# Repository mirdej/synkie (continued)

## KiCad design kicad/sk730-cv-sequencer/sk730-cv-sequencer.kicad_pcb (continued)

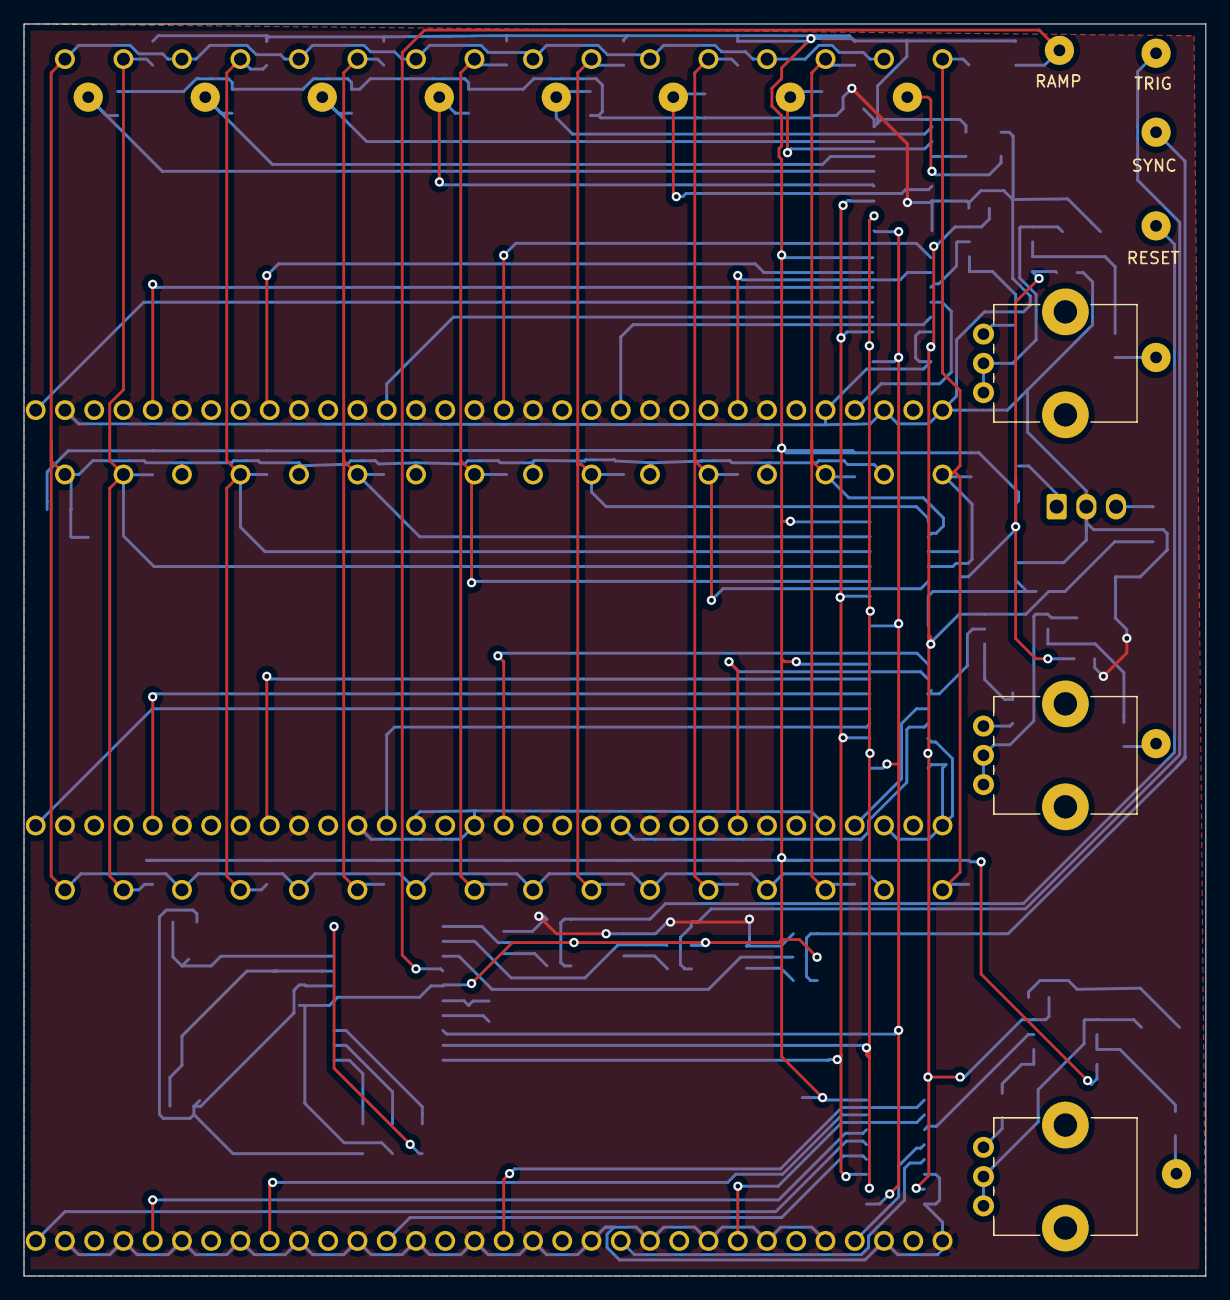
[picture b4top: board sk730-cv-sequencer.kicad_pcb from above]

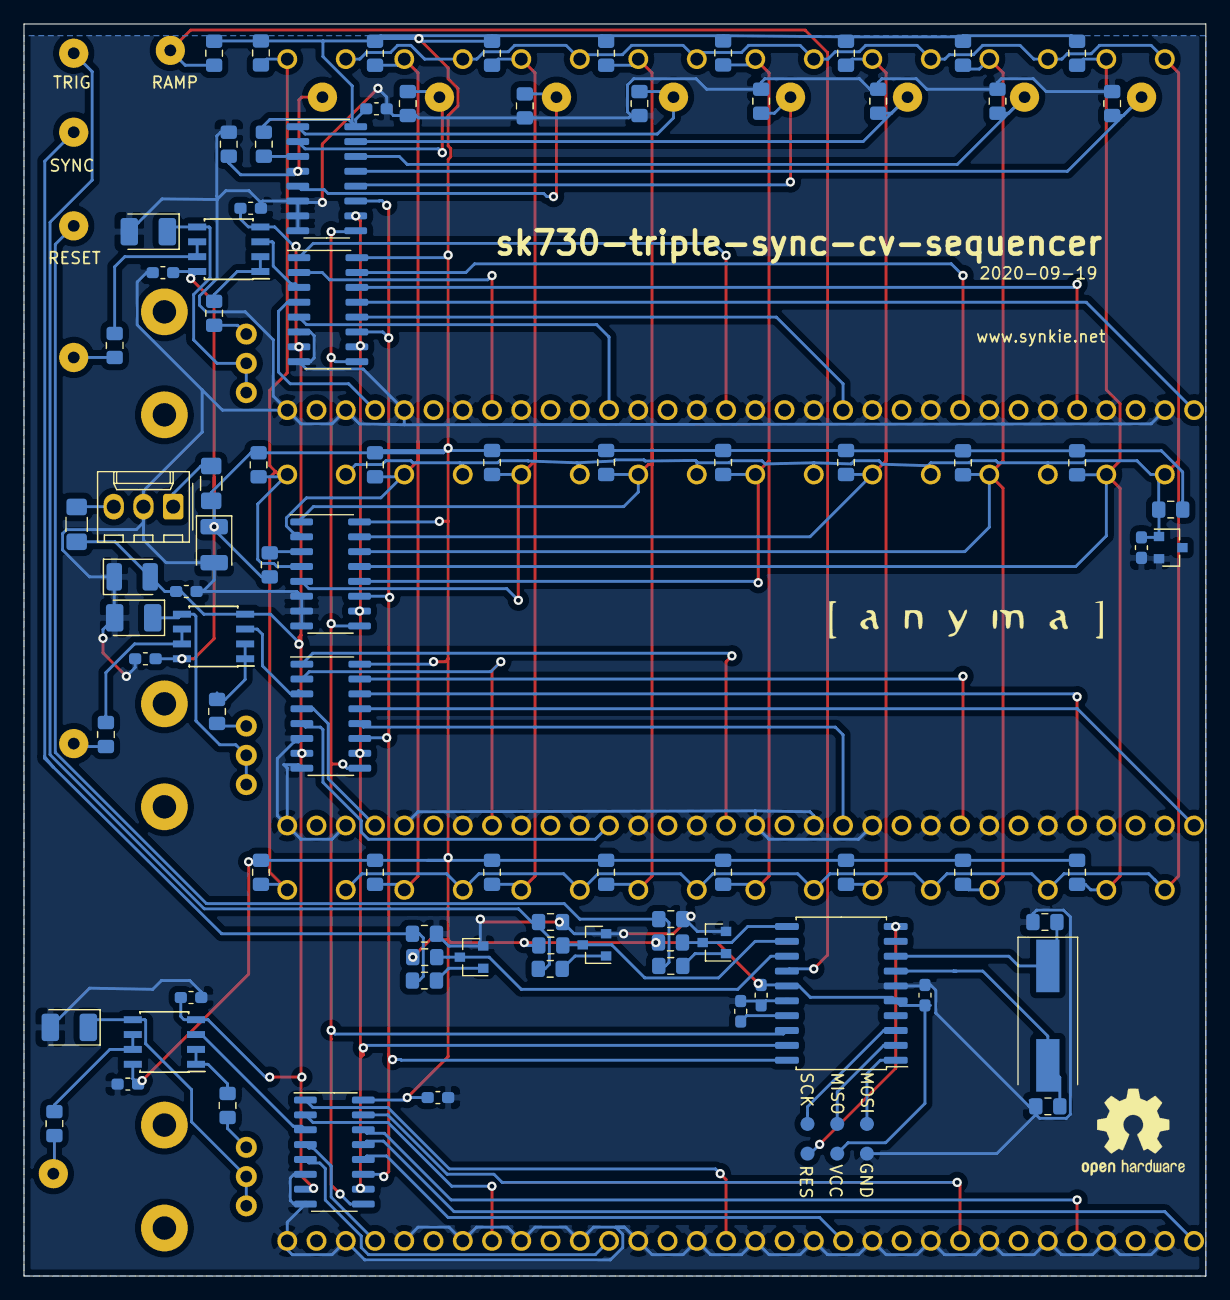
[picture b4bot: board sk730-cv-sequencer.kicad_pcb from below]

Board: 2 copper layers, 101.0 x 107.0 mm, 130 parts (103 on the bottom side), 86 nets.

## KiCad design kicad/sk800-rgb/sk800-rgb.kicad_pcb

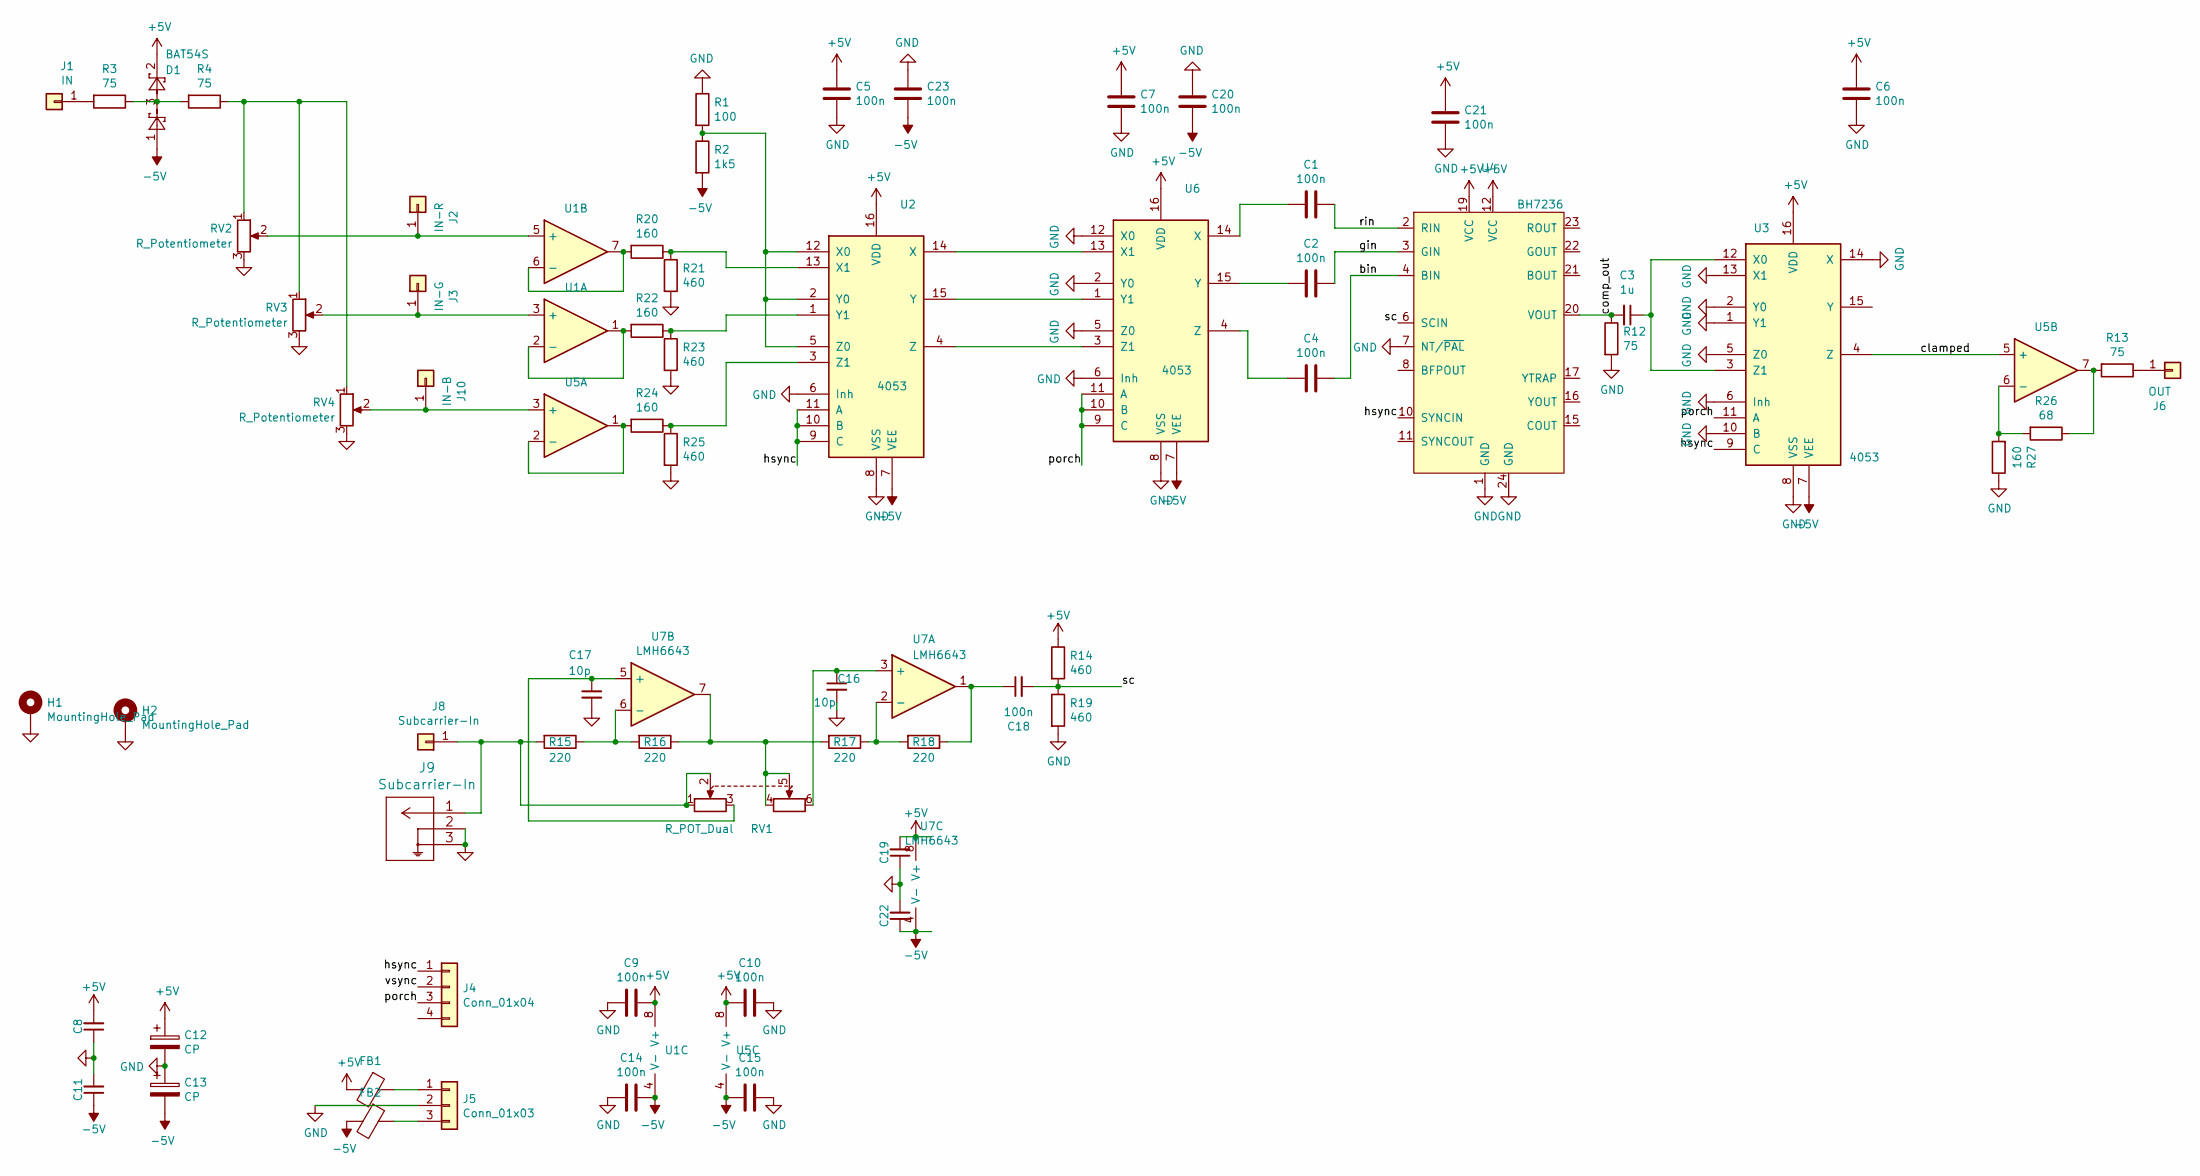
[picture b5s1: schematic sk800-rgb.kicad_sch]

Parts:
C1, C2, C4, C5, C6, C7, C8, C9, C10, C11, C14, C15, C18, C19, C20, C21, C22, C23: 100n; C_0603_1608Metric_Pad1.05x0.95mm_HandSolder
C3: 1u; C_0603_1608Metric_Pad1.05x0.95mm_HandSolder
C12, C13: CP; C_1206_3216Metric_Pad1.42x1.75mm_HandSolder
C16, C17: 10p; C_0805_2012Metric_Pad1.15x1.40mm_HandSolder
D1: BAT54S; SOT-23
FB1, FB2: Ferrite_Bead; L_0805_2012Metric_Pad1.15x1.40mm_HandSolder
H1, H2: MountingHole_Pad; MountingHole_3.2mm_M3_DIN965_Pad
J1: IN; Solderpad-SYNKIEPAD-2mm
J2: IN-R; Solderpad-SYNKIEPAD-2mm
J3: IN-G; Solderpad-SYNKIEPAD-2mm
J4: Conn_01x04; Molex_KK-254_AE-6410-04A_1x04_P2.54mm_Vertical
J5: Conn_01x03; Molex_KK-254_AE-6410-03A_1x03_P2.54mm_Vertical
J6: OUT; Solderpad-SYNKIEPAD-2mm
J8: Subcarrier-In; Solderpad-SYNKIEPAD-2mm
J9: Subcarrier-In; TE_UMCC_2337019-1
J10: IN-B; Solderpad-SYNKIEPAD-2mm
R1: 100; R_0805_2012Metric_Pad1.15x1.40mm_HandSolder
R2: 1k5; R_0805_2012Metric_Pad1.15x1.40mm_HandSolder
R3, R4, R12, R13: 75; R_0805_2012Metric_Pad1.15x1.40mm_HandSolder
R14, R19, R21, R23, R25: 460; R_0805_2012Metric_Pad1.15x1.40mm_HandSolder
R15, R16, R17, R18: 220; R_0805_2012Metric_Pad1.15x1.40mm_HandSolder
R20, R22, R24, R27: 160; R_0805_2012Metric_Pad1.15x1.40mm_HandSolder
R26: 68; R_0805_2012Metric_Pad1.15x1.40mm_HandSolder
RV1: R_POT_Dual; RK12L123
RV2, RV3, RV4: R_Potentiometer; Potentiometer_Uwe_100k
U1, U5: Opamp_Dual_Generic; SOIC-8_3.9x4.9mm_P1.27mm
U2, U3, U6: 4053; SOIC-16_3.9x9.9mm_P1.27mm
U4: BH7236; SOP-24_7.5x15.4mm_P1.27mm
U7: LMH6643; SOIC-8_3.9x4.9mm_P1.27mm

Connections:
+5V: C5.1, C6.1, C7.1, C8.2, C9.1, C10.2, C12.1, C19.2, C21.1, D1.2, FB1.2, R14.1, U1.8 (V+), U2.16 (VDD), U3.16 (VDD), U4.12 (VCC), U4.19 (VCC), U5.8 (V+), U6.16 (VDD), U7.8 (V+)
-5V: C11.1, C13.2, C14.1, C15.2, C20.2, C22.1, C23.2, D1.1, FB2.2, R2.2, U1.4 (V-), U2.7 (VEE), U3.7 (VEE), U5.4 (V-), U6.7 (VEE), U7.4 (V-)
/bin: C4.1, U4.4 (BIN)
/clamped: U3.4 (Z), U5.5 (+)
/comp_out: C3.2, R12.1, U4.20 (VOUT)
/gin: C2.1, U4.3 (GIN)
/hsync: J4.1, U2.9 (C), U2.10 (B), U2.11 (A), U3.9 (C), U4.10 (SYNCIN)
/porch: J4.3, U3.11 (A), U6.9 (C), U6.10 (B), U6.11 (A)
/rin: C1.1, U4.2 (RIN)
/sc: C18.2, R14.2, R19.1, U4.6 (SCIN)
/vsync: J4.2
GND: C5.2, C6.2, C7.2, C8.1, C9.2, C10.1, C11.2, C12.2, C13.1, C14.2, C15.1, C16.2, C17.2, C19.1, C20.1, C21.2, C22.2, C23.1, H1.1, H2.1, J5.2, J9.2, J9.3, R1.1, R12.2, R19.2, R21.2, R23.2, R25.2, R27.1, RV2.3, RV3.3, RV4.3, U2.6 (Inh), U2.8 (VSS), U3.1 (Y1), U3.2 (Y0), U3.5 (Z0), U3.6 (Inh), U3.8 (VSS), U3.10 (B), U3.13 (X1), U3.14 (X), U4.1 (GND), U4.7 (NT/~PAL), U4.24 (GND), U6.2 (Y0), U6.5 (Z0), U6.6 (Inh), U6.8 (VSS), U6.12 (X0)
unnamed: C18.1, R18.1, U7.1
unnamed: D1.3, R3.1, R4.2
unnamed: J1.1, R3.2
unnamed: J2.1, RV2.2, U1.5 (+)
unnamed: J3.1, RV3.2, U1.3 (+)
unnamed: FB1.1, J5.1
unnamed: FB2.1, J5.3
unnamed: J6.1, R13.1
unnamed: J8.1, J9.1, R15.2, RV1.1, RV1.2
unnamed: J10.1, RV4.2, U5.3 (+)
unnamed: R4.1, RV2.1, RV3.1, RV4.1
unnamed: R13.2, R26.1, U5.7
unnamed: R16.1, R17.2, RV1.4, RV1.5, U7.7
unnamed: R22.2, U1.1, U1.2 (-)
unnamed: R20.2, U1.6 (-), U1.7
unnamed: R1.2, R2.1, U2.2 (Y0), U2.5 (Z0), U2.12 (X0)
unnamed: R20.1, R21.1, U2.13 (X1)
unnamed: U2.14 (X), U6.13 (X1)
unnamed: R22.1, R23.1, U2.1 (Y1)
unnamed: U2.15 (Y), U6.1 (Y1)
unnamed: R24.1, R25.1, U2.3 (Z1)
unnamed: U2.4 (Z), U6.3 (Z1)
unnamed: C3.1, U3.3 (Z1), U3.12 (X0)
unnamed: R24.2, U5.1, U5.2 (-)
unnamed: R26.2, R27.2, U5.6 (-)
unnamed: C1.2, U6.14 (X)
unnamed: C2.2, U6.15 (Y)
unnamed: C4.2, U6.4 (Z)
unnamed: C16.1, RV1.6, U7.3 (+)
unnamed: R17.1, R18.2, U7.2 (-)
unnamed: C17.1, RV1.3, U7.5 (+)
unnamed: R15.1, R16.2, U7.6 (-)

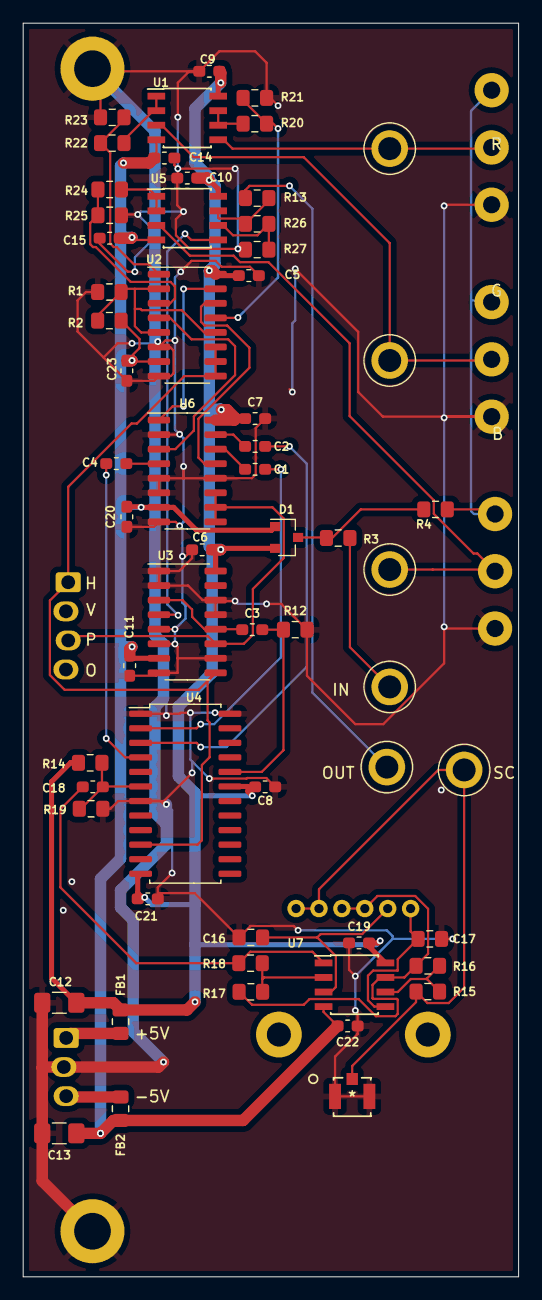
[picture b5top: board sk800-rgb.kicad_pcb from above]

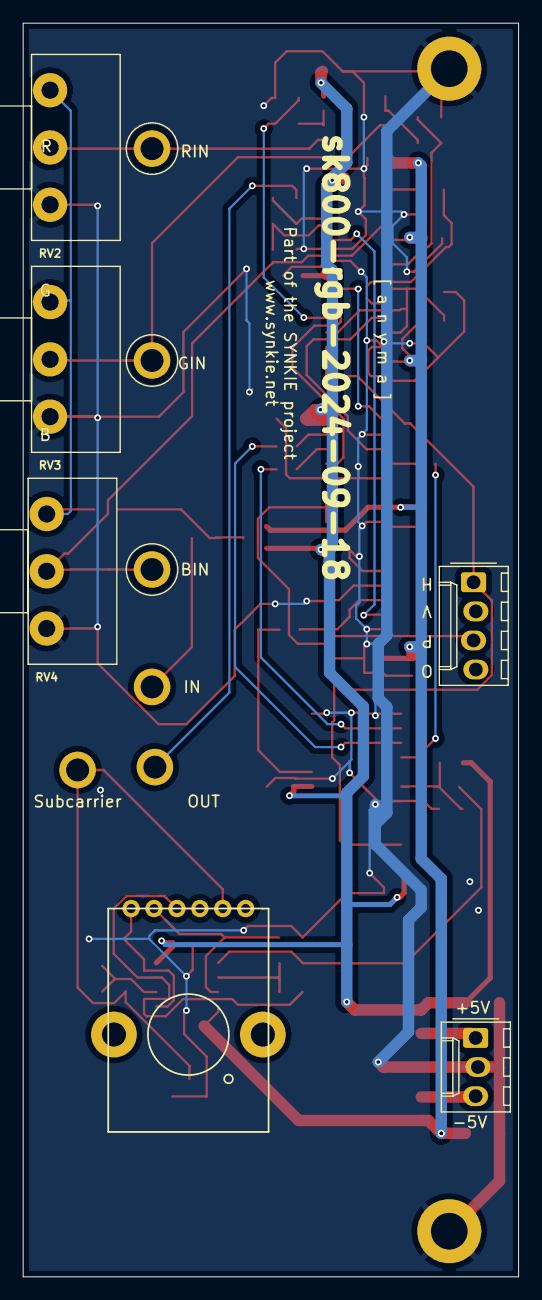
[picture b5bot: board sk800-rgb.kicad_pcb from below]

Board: 2 copper layers, 43.2 x 109.4 mm, 68 parts (6 on the bottom side), 43 nets.

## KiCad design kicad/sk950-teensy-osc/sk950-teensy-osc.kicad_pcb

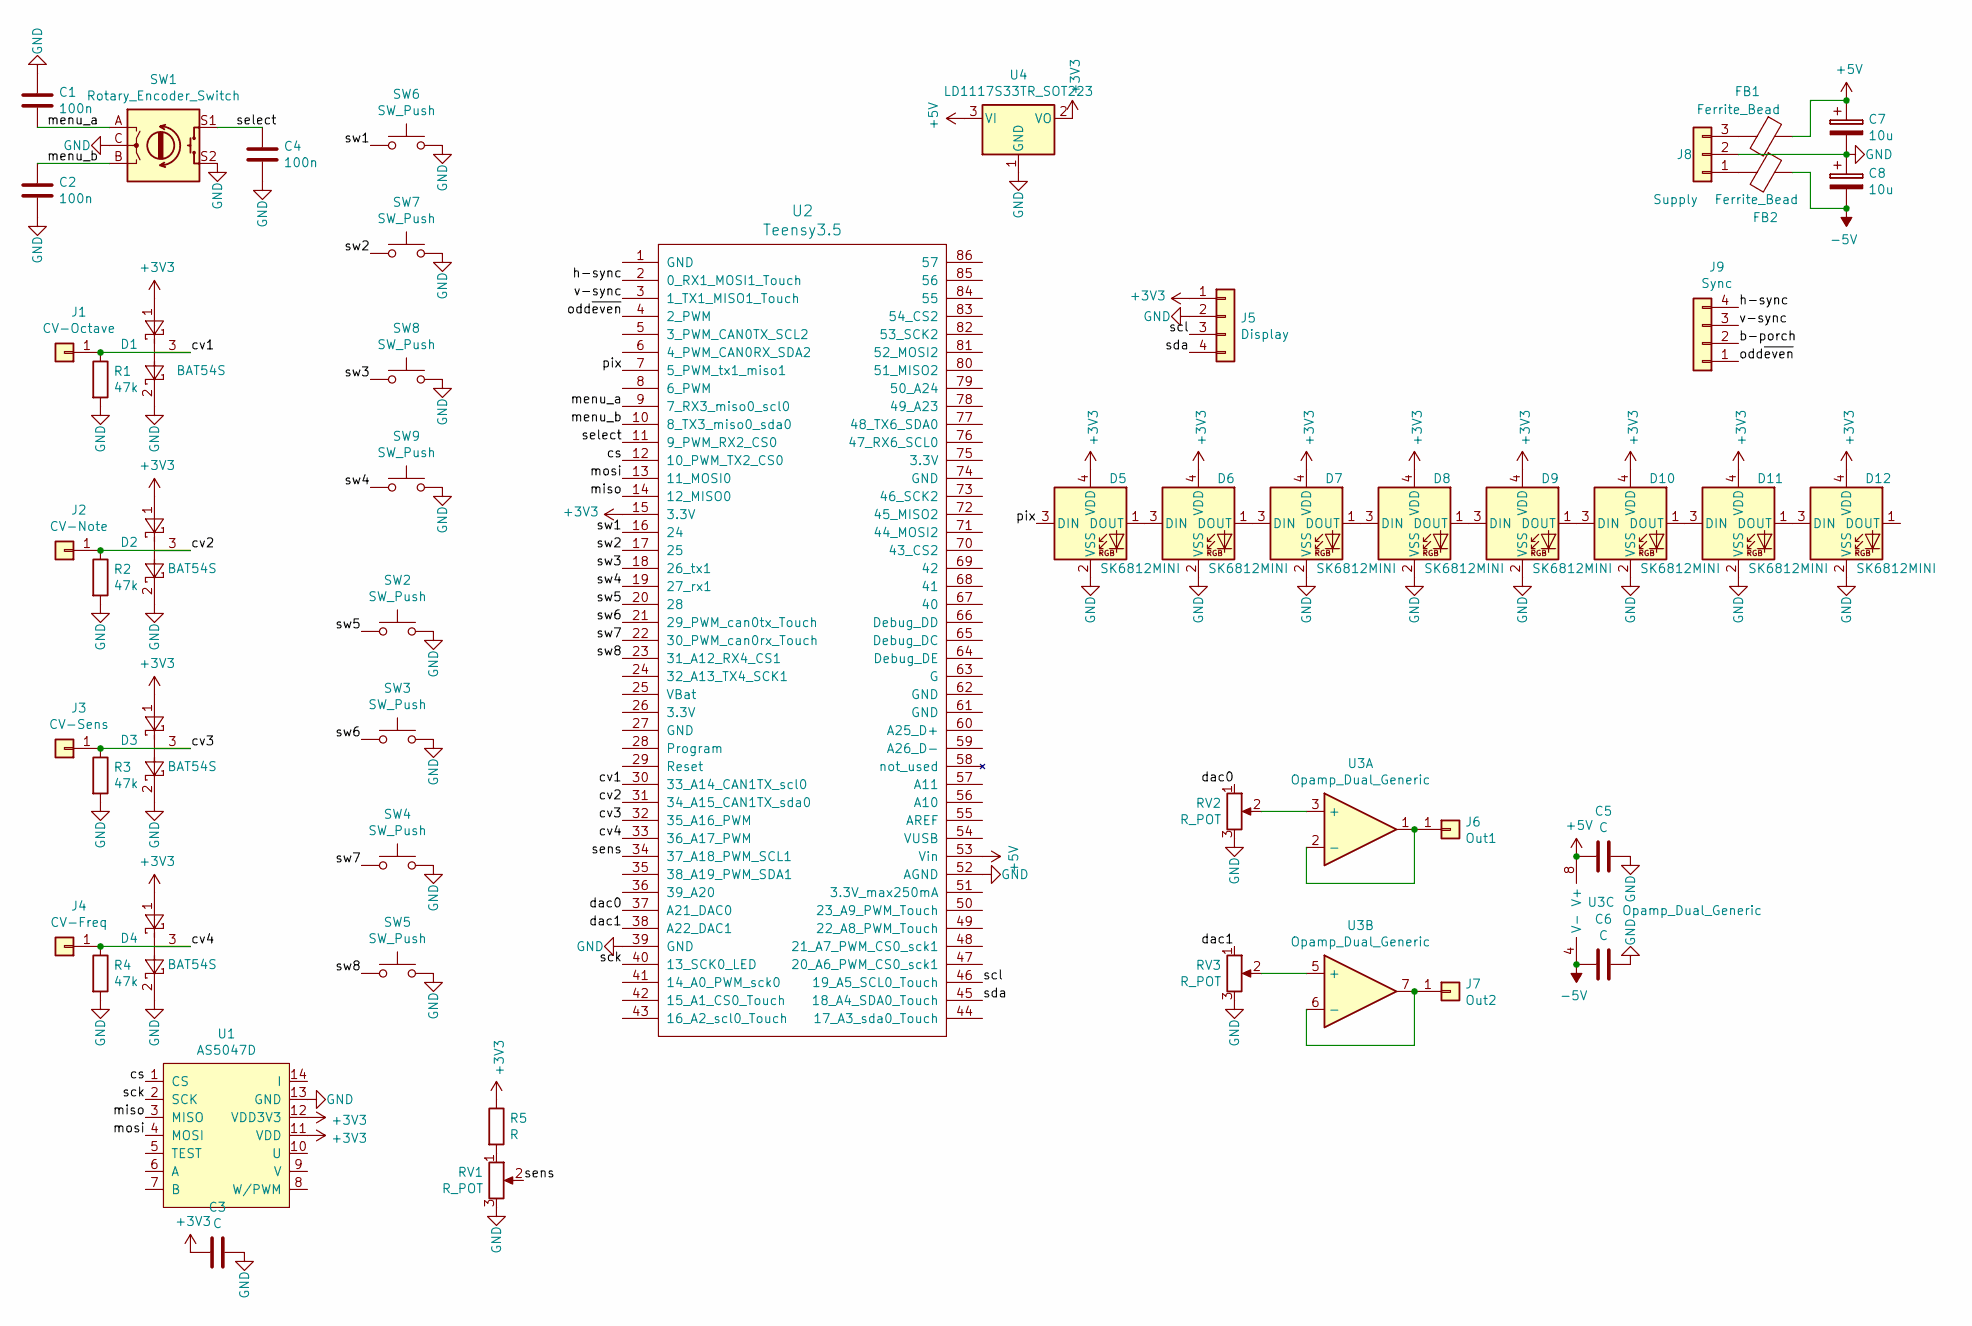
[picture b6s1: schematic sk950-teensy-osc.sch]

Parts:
C1, C2, C4: 100n; C_0603_1608Metric_Pad1.05x0.95mm_HandSolder
C3, C5, C6: C; C_0603_1608Metric_Pad1.05x0.95mm_HandSolder
C7, C8: 10u; CP_EIA-3528-21_Kemet-B
D1, D2, D3, D4: BAT54S; SOT-23
D5, D6, D7, D8, D9, D10, D11, D12: SK6812MINI; LED_SK6812MINI_PLCC4_3.5x3.5mm_P1.75mm
FB1, FB2: Ferrite_Bead; L_1206_3216Metric_Pad1.42x1.75mm_HandSolder
J1: CV-Octave; Solderpad_1mm
J2: CV-Note; Solderpad_1mm
J3: CV-Sens; Solderpad_1mm
J4: CV-Freq; Solderpad_1mm
J5: Display; Bangood_I2C_Display
J6: Out1; Solderpad_1mm
J7: Out2; Solderpad_1mm
J8: Supply; Molex_KK-254_AE-6410-03A_1x03_P2.54mm_Vertical
J9: Sync; Molex_KK-254_AE-6410-04A_1x04_P2.54mm_Vertical
R1, R2, R3, R4: 47k; R_1206_3216Metric_Pad1.42x1.75mm_HandSolder
R5: R; R_1206_3216Metric_Pad1.42x1.75mm_HandSolder
RV1: R_POT; Potentiometer_Alps_RK09K_Single_Vertical
RV2, RV3: R_POT; Potentiometer_ACP_CA14-H4_Horizontal
SW1: Rotary_Encoder_Switch; RotaryEncoder_Alps_EC12E-Switch_Vertical_H20mm_CircularMoun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
SW2, SW3, SW4, SW5, SW6, SW7, SW8, SW9: SW_Push; Alps_Tactile_Switch
U1: AS5047D; TSSOP-14_4.4x5mm_P0.65mm
U2: Teensy3.5; Teensy35_36-light
U3: Opamp_Dual_Generic; SOIC-8_3.9x4.9mm_P1.27mm
U4: LD1117S33TR_SOT223; SOT-223-3_TabPin2

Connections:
+3V3: C3.2, D1.1, D2.1, D3.1, D4.1, D5.4 (VDD), D6.4 (VDD), D7.4 (VDD), D8.4 (VDD), D9.4 (VDD), D10.4 (VDD), D11.4 (VDD), D12.4 (VDD), J5.1, R5.1, U1.11 (VDD), U1.12 (VDD3V3), U2.15 (3.3V), U4.2 (VO)
+5V: C5.2, C7.1, FB1.1, U2.53 (Vin), U3.8 (V+), U4.3 (VI)
-5V: C6.2, C8.2, FB2.1, U3.4 (V-)
/cs: U1.1 (CS), U2.12 (10_PWM_TX2_CS0)
/cv1: D1.3, J1.1, R1.1, U2.30 (33_A14_CAN1TX_scl0)
/cv2: D2.3, J2.1, R2.1, U2.31 (34_A15_CAN1TX_sda0)
/cv3: D3.3, J3.1, R3.1, U2.32 (35_A16_PWM)
/cv4: D4.3, J4.1, R4.1, U2.33 (36_A17_PWM)
/dac0: RV2.1, U2.37 (A21_DAC0)
/dac1: RV3.1, U2.38 (A22_DAC1)
/h-sync: J9.4, U2.2 (0_RX1_MOSI1_Touch)
/menu_a: C1.2, SW1.A, U2.9 (7_RX3_miso0_scl0)
/menu_b: C2.1, SW1.B, U2.10 (8_TX3_miso0_sda0)
/miso: U1.3 (MISO), U2.14 (12_MISO0)
/mosi: U1.4 (MOSI), U2.13 (11_MOSI0)
/odd~even: J9.1, U2.4 (2_PWM)
/pix: D5.3 (DIN), U2.7 (5_PWM_tx1_miso1)
/sck: U1.2 (SCK), U2.40 (13_SCK0_LED)
/scl: J5.3, U2.46 (19_A5_SCL0_Touch)
/sda: J5.4, U2.45 (18_A4_SDA0_Touch)
/select: C4.1, SW1.S1, U2.11 (9_PWM_RX2_CS0)
/sens: RV1.2, U2.34 (37_A18_PWM_SCL1)
/sw1: SW6.2, U2.16 (24)
/sw2: SW7.2, U2.17 (25)
/sw3: SW8.2, U2.18 (26_tx1)
/sw4: SW9.2, U2.19 (27_rx1)
/sw5: SW2.2, U2.20 (28)
/sw6: SW3.2, U2.21 (29_PWM_can0tx_Touch)
/sw7: SW4.2, U2.22 (30_PWM_can0rx_Touch)
/sw8: SW5.2, U2.23 (31_A12_RX4_CS1)
/v-sync: J9.3, U2.3 (1_TX1_MISO1_Touch)
GND: C1.1, C2.2, C3.1, C4.2, C5.1, C6.1, C7.2, C8.1, D1.2, D2.2, D3.2, D4.2, D5.2 (VSS), D6.2 (VSS), D7.2 (VSS), D8.2 (VSS), D9.2 (VSS), D10.2 (VSS), D11.2 (VSS), D12.2 (VSS), J5.2, J8.2, R1.2, R2.2, R3.2, R4.2, RV1.3, RV2.3, RV3.3, SW1.C, SW1.S2, SW2.1, SW3.1, SW4.1, SW5.1, SW6.1, SW7.1, SW8.1, SW9.1, U1.13 (GND), U2.39 (GND), U2.52 (AGND), U4.1 (GND)
unnamed: D5.1 (DOUT), D6.3 (DIN)
unnamed: D6.1 (DOUT), D7.3 (DIN)
unnamed: D7.1 (DOUT), D8.3 (DIN)
unnamed: D8.1 (DOUT), D9.3 (DIN)
unnamed: D10.1 (DOUT), D11.3 (DIN)
unnamed: D9.1 (DOUT), D10.3 (DIN)
unnamed: D11.1 (DOUT), D12.3 (DIN)
unnamed: FB1.2, J8.3
unnamed: FB2.2, J8.1
unnamed: J6.1, U3.1, U3.2 (-)
unnamed: J7.1, U3.6 (-), U3.7
unnamed: R5.2, RV1.1
unnamed: RV2.2, U3.3 (+)
unnamed: RV3.2, U3.5 (+)

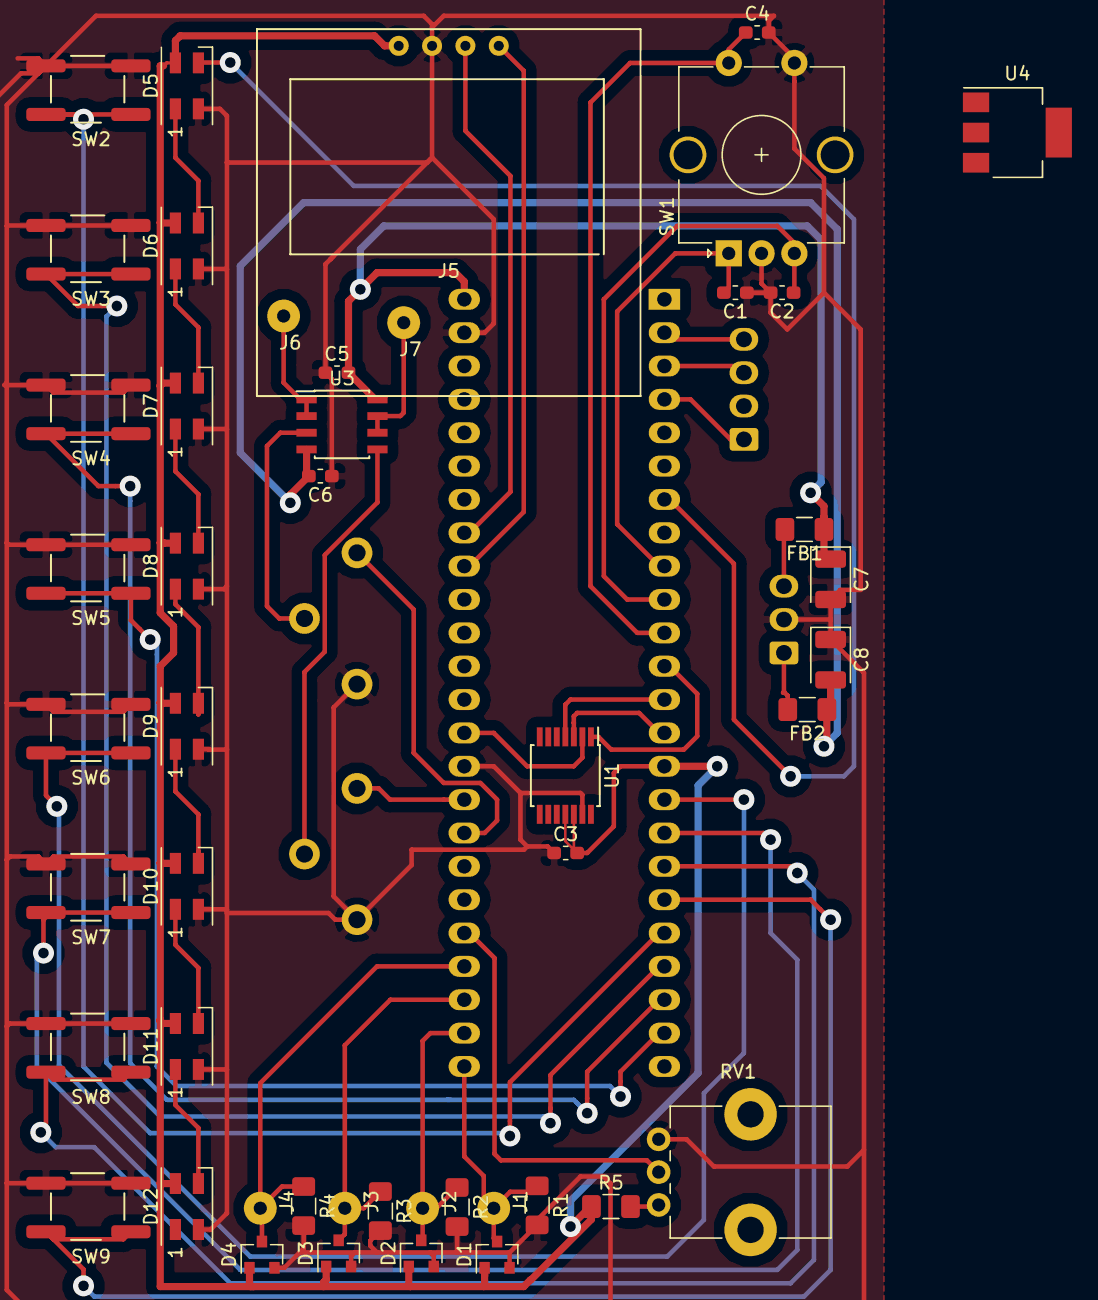
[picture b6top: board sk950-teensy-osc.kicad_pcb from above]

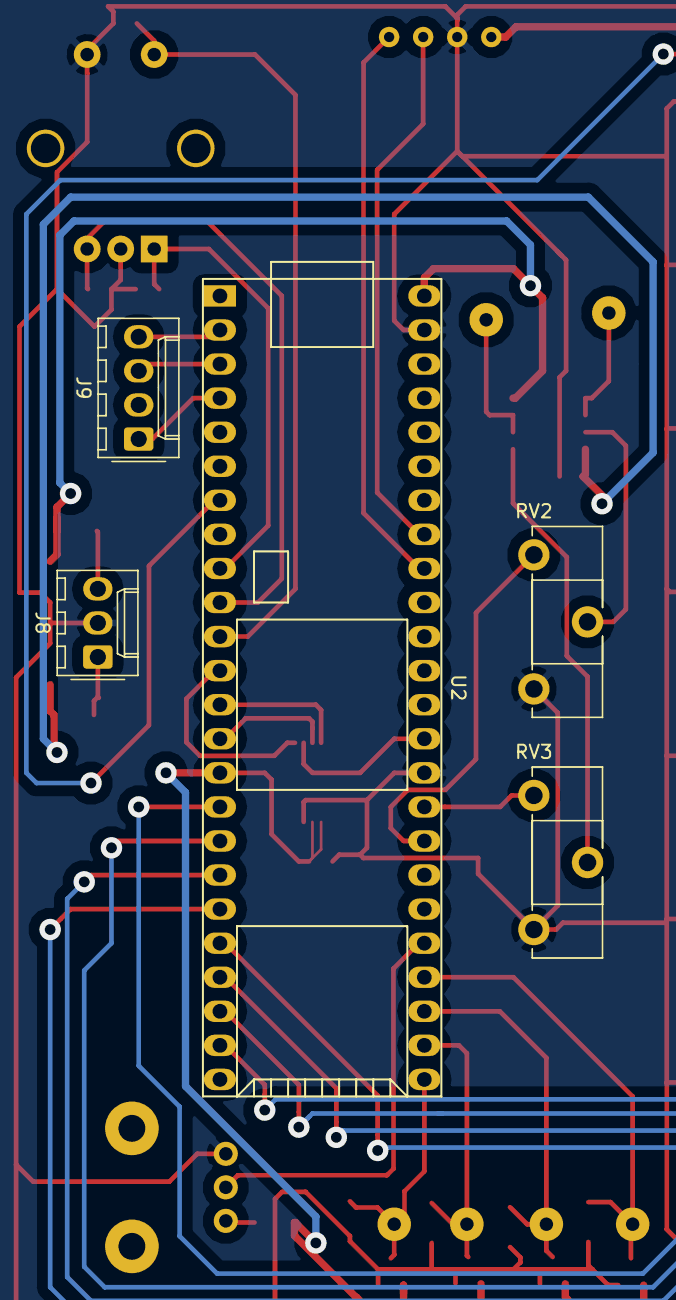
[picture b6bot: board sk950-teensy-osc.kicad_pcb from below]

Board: 2 copper layers, 52 parts (5 on the bottom side), 46 nets.

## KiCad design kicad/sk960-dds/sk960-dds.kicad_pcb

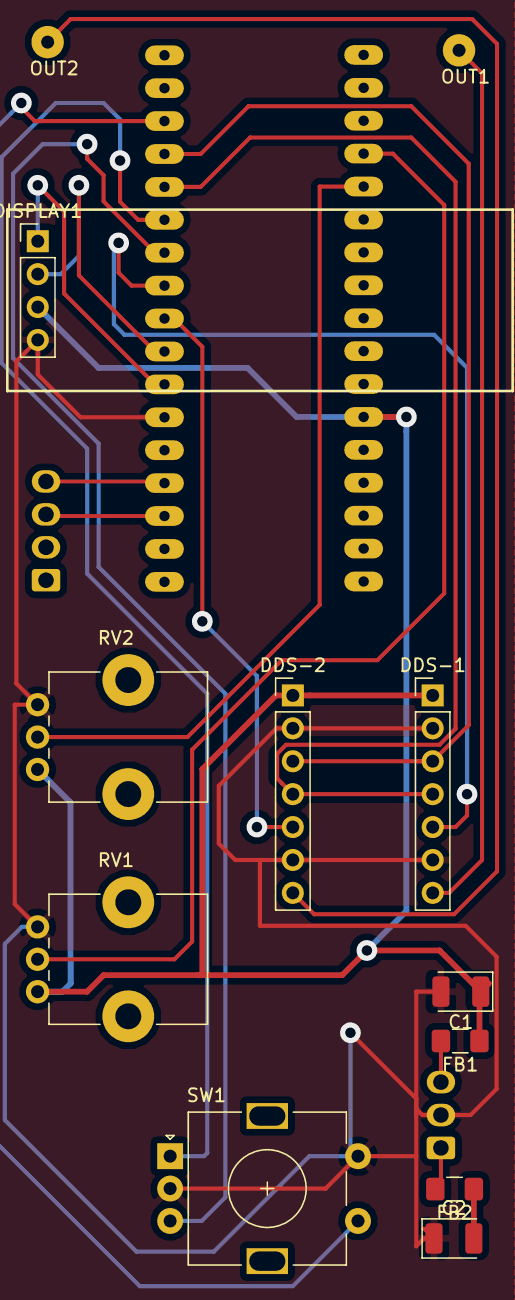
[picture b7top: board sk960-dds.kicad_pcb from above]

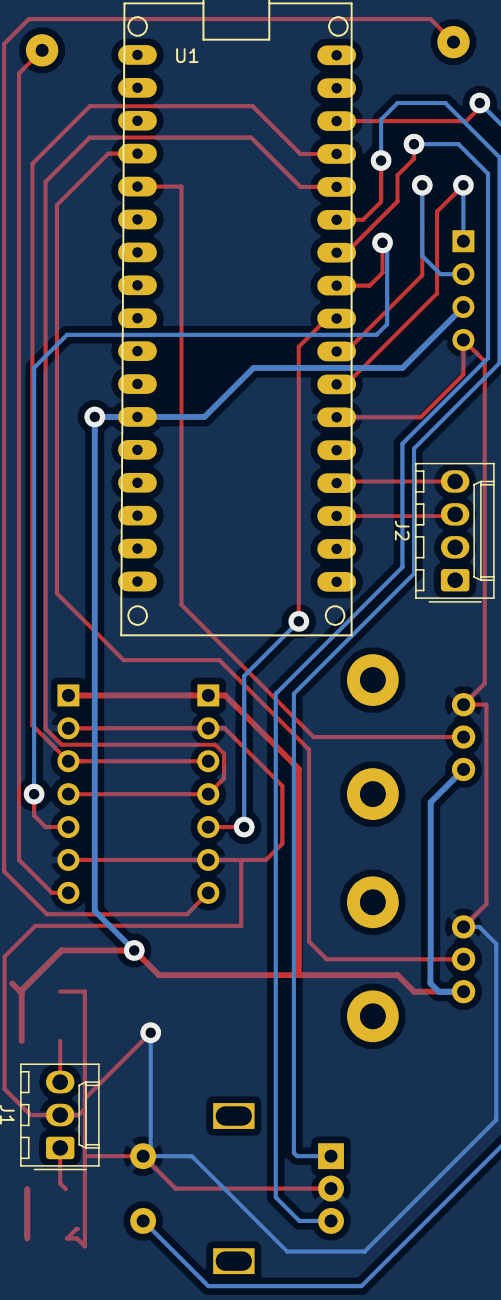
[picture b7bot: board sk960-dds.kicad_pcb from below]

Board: 2 copper layers, 15 parts (3 on the bottom side), 20 nets.

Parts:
C1, C2: 10u; CP_EIA-3528-21_Kemet-B
DDS-1, DDS-2: Conn_01x07; PinHeader_1x07_P2.54mm_Vertical
DISPLAY1: Conn_01x04; PinHeader_1x04_P2.54mm_Vertical
FB1, FB2: Ferrite_Bead; L_1206_3216Metric_Pad1.42x1.75mm_HandSolder
J1: Supply; Molex_KK-254_AE-6410-03A_1x03_P2.54mm_Vertical
J2: Sync; Molex_KK-254_AE-6410-04A_1x04_P2.54mm_Vertical
OUT1, OUT2: Conn_01x01; Solderpad_1mm
RV1, RV2: R_POT; Potentiometer_Alps_RK09K_Single_Vertical
SW1: Rotary_Encoder_Switch; RotaryEncoder_Alps_EC11E-Switch_Vertical_H20mm
U1: ArduinoMicro

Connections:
+5V: C1.1, DDS-1.1, DDS-2.1, DISPLAY1.3, FB1.1, RV1.1, RV2.1, U1.12
-5V: C2.2, FB2.1
/A: SW1.A, U1.29
/B: SW1.B, U1.28
/CS1: DDS-1.5, U1.27
/CS2: DDS-2.5, U1.26
/PHASE: RV2.2, U1.5
/SCL: DISPLAY1.2, U1.25
/SCLK: DDS-1.4, DDS-2.4, U1.30
/SDA: DISPLAY1.1, U1.24
/SDATA: DDS-1.3, DDS-2.3, U1.31
/SPEED: RV1.2, U1.4
/h-sync: J2.4, U1.21
/switch: SW1.S1, U1.32
/v-sync: J2.3, U1.20
GND: C1.2, C2.1, DDS-1.2, DDS-1.6, DDS-2.2, DDS-2.6, DISPLAY1.4, J1.2, RV1.3, RV2.3, SW1.C, SW1.S2, U1.23
unnamed: DDS-1.7, OUT1.1
unnamed: DDS-2.7, OUT2.1
unnamed: FB1.2, J1.3
unnamed: FB2.2, J1.1
